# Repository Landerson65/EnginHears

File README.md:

# EnginHears
LCBC Hearing Aid Development Platform

This project intended to develop a low cost, socially destigmatized hearing aid design. Despite hearing loss being so prominent, the average cost of hearing aids is $2,300 per unit, putting hearing aids out of reach of many low- to middle-income families. In addition, many people who need and can afford hearing aids choose not to buy them, as their bulky aesthetic increases social stigma. To combat these current market limitations, the EnginHears developed a Low Cost Bone Conduction (LCBC) Hearing Aid Development Platform.

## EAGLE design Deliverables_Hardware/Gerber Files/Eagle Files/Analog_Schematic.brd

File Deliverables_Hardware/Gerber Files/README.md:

This folder contains all of the necessary files in order
to have the hardware system printed circuit board manufactured. 
This includes drill files, copper layers, silkscreen layers,
board profile and more. These gerber files were created using Autodesk Eagle.

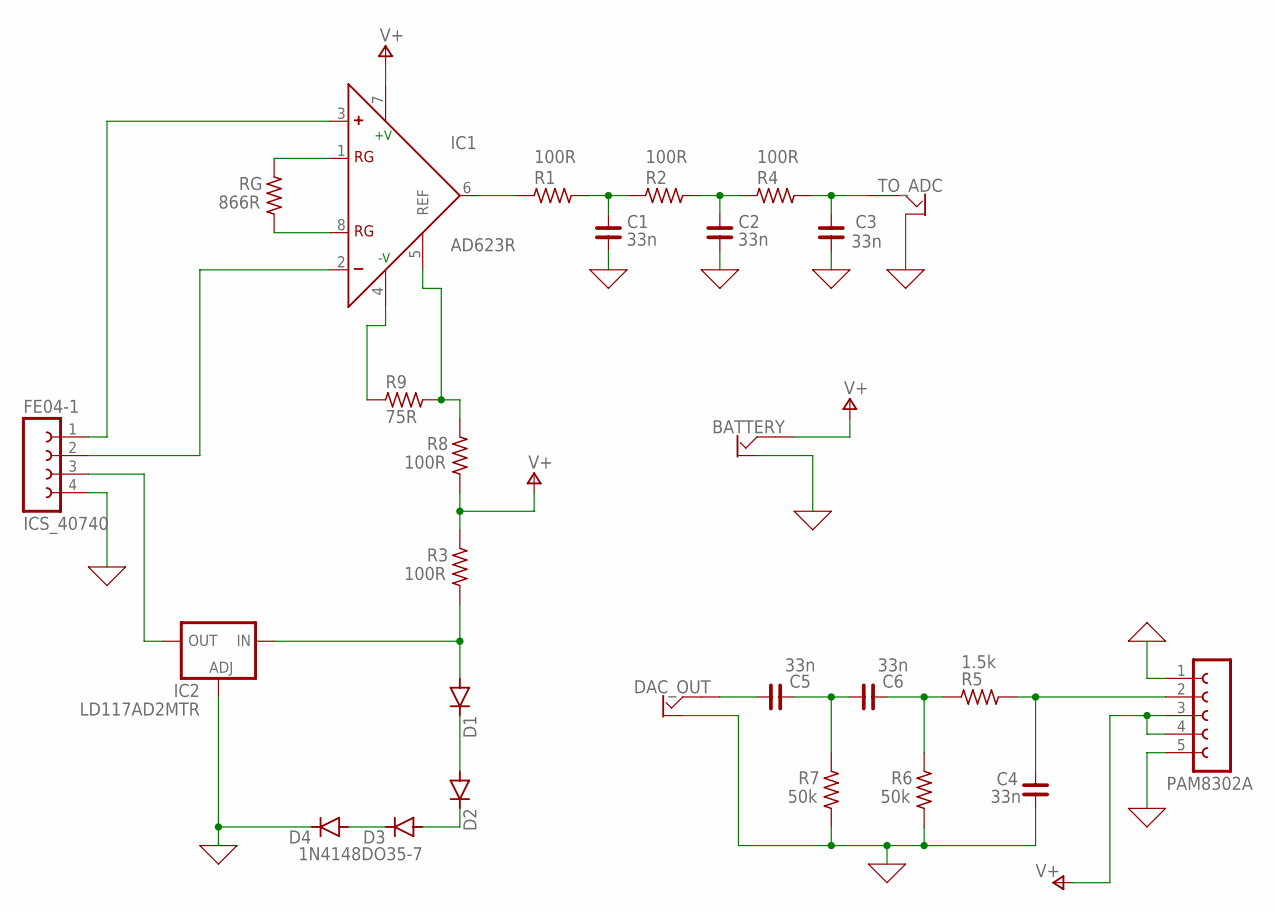
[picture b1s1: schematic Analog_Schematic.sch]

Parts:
BATTERY: OFFBOARD2JACKALT
C1, C2, C3, C4, C5, C6: 33n; C0603
D1, D2, D3, D4: 1N4148DO35-7; DO35-7
DAC_OUT: OFFBOARD2JACKALT
IC1: AD623R; SO8
IC2: LD117AD2MTR; D2PACK
ICS_40740: FE04-1
PAM8302A: FE05-1
R1, R2, R3, R4, R8: 100R; R0603
R5: 1.5k; R0603
R6, R7: 50k; R0603
R9: 75R; R0603
RG: 866R; R0603
TO_ADC: OFFBOARD2JACKALT

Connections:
0: BATTERY.GND, C1.2, C2.2, C3.2, C4.2, D4.C, DAC_OUT.GND, IC2.1 (ADJ), ICS_40740.4, PAM8302A.1, PAM8302A.5, R6.1, R7.1, TO_ADC.GND
unnamed: IC1.8 (RG), RG.1
unnamed: IC1.1 (RG), RG.2
unnamed: IC1.6 (OUT), R1.1
unnamed: IC1.4 (-V), R9.1
unnamed: IC1.5 (REF), R8.2, R9.2
unnamed: D1.A, IC2.3 (IN), R3.1
unnamed: D1.C, D2.A
unnamed: D2.C, D3.A
unnamed: D3.C, D4.A
unnamed: IC2.2 (OUT), ICS_40740.3
unnamed: IC1.3 (+), ICS_40740.1
unnamed: IC1.2 (-), ICS_40740.2
unnamed: C1.1, R1.2, R2.1
unnamed: C2.1, R2.2, R4.1
unnamed: C3.1, R4.2, TO_ADC.SIGNAL
unnamed: C5.1, DAC_OUT.SIGNAL
unnamed: C5.2, C6.1, R7.2
unnamed: C6.2, R5.1, R6.2
unnamed: C4.1, PAM8302A.2, R5.2
V+: BATTERY.SIGNAL, IC1.7 (+V), PAM8302A.3, PAM8302A.4, R3.2, R8.1

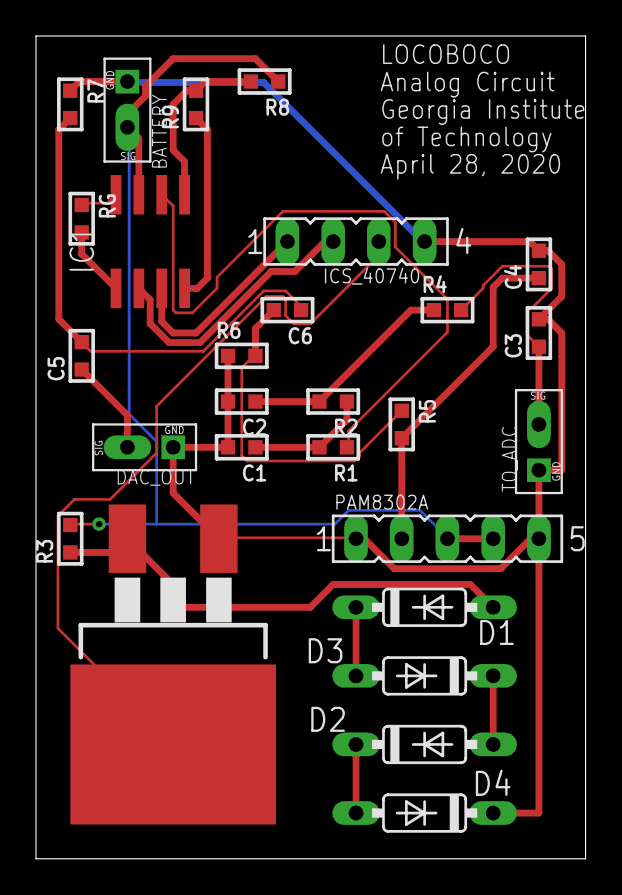
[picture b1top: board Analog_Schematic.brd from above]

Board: 2 copper layers, 30.5 x 45.7 mm, 27 parts (0 on the bottom side), 21 nets.

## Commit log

2020-04-29 Hardware Deliverables

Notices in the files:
parts and their libraries:
rc-master-smd: Copyright (C) 2007, Bob Starr
